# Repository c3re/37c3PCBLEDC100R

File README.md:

# 37c3PCBLEDC100R
Coaster for your drinks with option for LED and microcontroller upgrade.

## Rev.1
### Electrical connections
Important: Do not power the board by USB and an external power supply at the same time!
The Din pin of the first LED is connected to pin D4 (GPIO2) of the Wemos D1 mini. Two of the mounting holes are connected to GND, two of the holes are connected to 5V. You can use this feature to stack multiple 37c3PCBLEDc100R Boards with brass spacers.
### Bug
The revision 1 contains an error in the PCB-Layout! The error affects all LED footprints, the LED pins 1 & 2 are swapped. To fix the Bug, we recommend to bend pin 2 around the PCB edge and solder it on the bottom to the squared pad.

## Rev.2
Bugfixed 
## License
The 37c3 Logo and the dithered image of the bolt cutter were created by Robokid // Luis F. Masallera and Euler Void \
37c3PCBLEDC100R © 2023 by c3RE is licensed under CC BY 4.0. To view a copy of this license, \
visit http://creativecommons.org/licenses/by/4.0/

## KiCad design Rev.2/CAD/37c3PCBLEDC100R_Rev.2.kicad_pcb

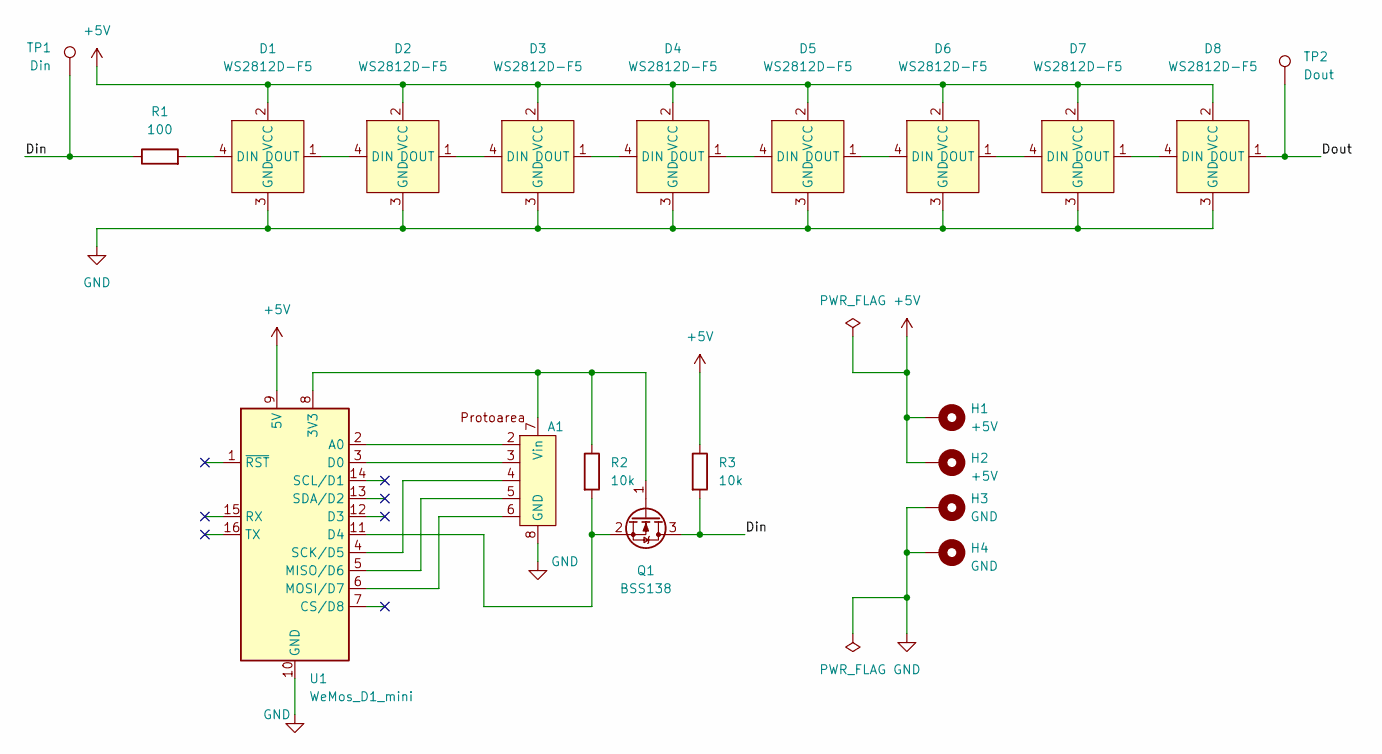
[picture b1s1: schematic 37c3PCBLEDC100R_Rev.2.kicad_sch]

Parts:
A1: Protoarea
D1, D2, D3, D4, D5, D6, D7, D8: WS2812D-F5; WS2812_THT; LCSC Part # C190565
H1, H2: +5V; MountingHole_3.2mm_M3_DIN965_Pad
H3, H4: GND; MountingHole_3.2mm_M3_DIN965_Pad
Q1: BSS138; SOT-23
R1: 100; 1206_combi_handsolder
R2, R3: 10k; 1206_combi_handsolder
TP1: Din; TestPoint_THTPad_D2.5mm_Drill1.2mm
TP2: Dout; TestPoint_THTPad_D2.5mm_Drill1.2mm
U1: WeMos_D1_mini; WEMOS_D1_mini_light

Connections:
+5V: D1.2 (VCC), D2.2 (VCC), D3.2 (VCC), D4.2 (VCC), D5.2 (VCC), D6.2 (VCC), D7.2 (VCC), D8.2 (VCC), H1.1, H2.1, R3.1, U1.9 (5V)
/Din: Q1.3 (D), R1.1, R3.2, TP1.1; also elsewhere on the board
/Dout: D8.1 (DOUT), TP2.1; also elsewhere on the board
GND: A1.8 (GND), D1.3 (GND), D2.3 (GND), D3.3 (GND), D4.3 (GND), D5.3 (GND), D6.3 (GND), D7.3 (GND), D8.3 (GND), H3.1, H4.1, U1.10 (GND)
unnamed: A1.7 (Vin), Q1.1 (G), R2.1, U1.8 (3V3)
unnamed: D1.4 (DIN), R1.2
unnamed: D1.1 (DOUT), D2.4 (DIN)
unnamed: D2.1 (DOUT), D3.4 (DIN)
unnamed: D3.1 (DOUT), D4.4 (DIN)
unnamed: D4.1 (DOUT), D5.4 (DIN)
unnamed: D5.1 (DOUT), D6.4 (DIN)
unnamed: D6.1 (DOUT), D7.4 (DIN)
unnamed: D7.1 (DOUT), D8.4 (DIN)
unnamed: Q1.2 (S), R2.2, U1.11 (D4)
unnamed: A1.2, U1.2 (A0)
unnamed: A1.3, U1.3 (D0)
unnamed: A1.5, U1.5 (MISO/D6)
unnamed: A1.6, U1.6 (MOSI/D7)
unnamed: A1.4, U1.4 (SCK/D5)

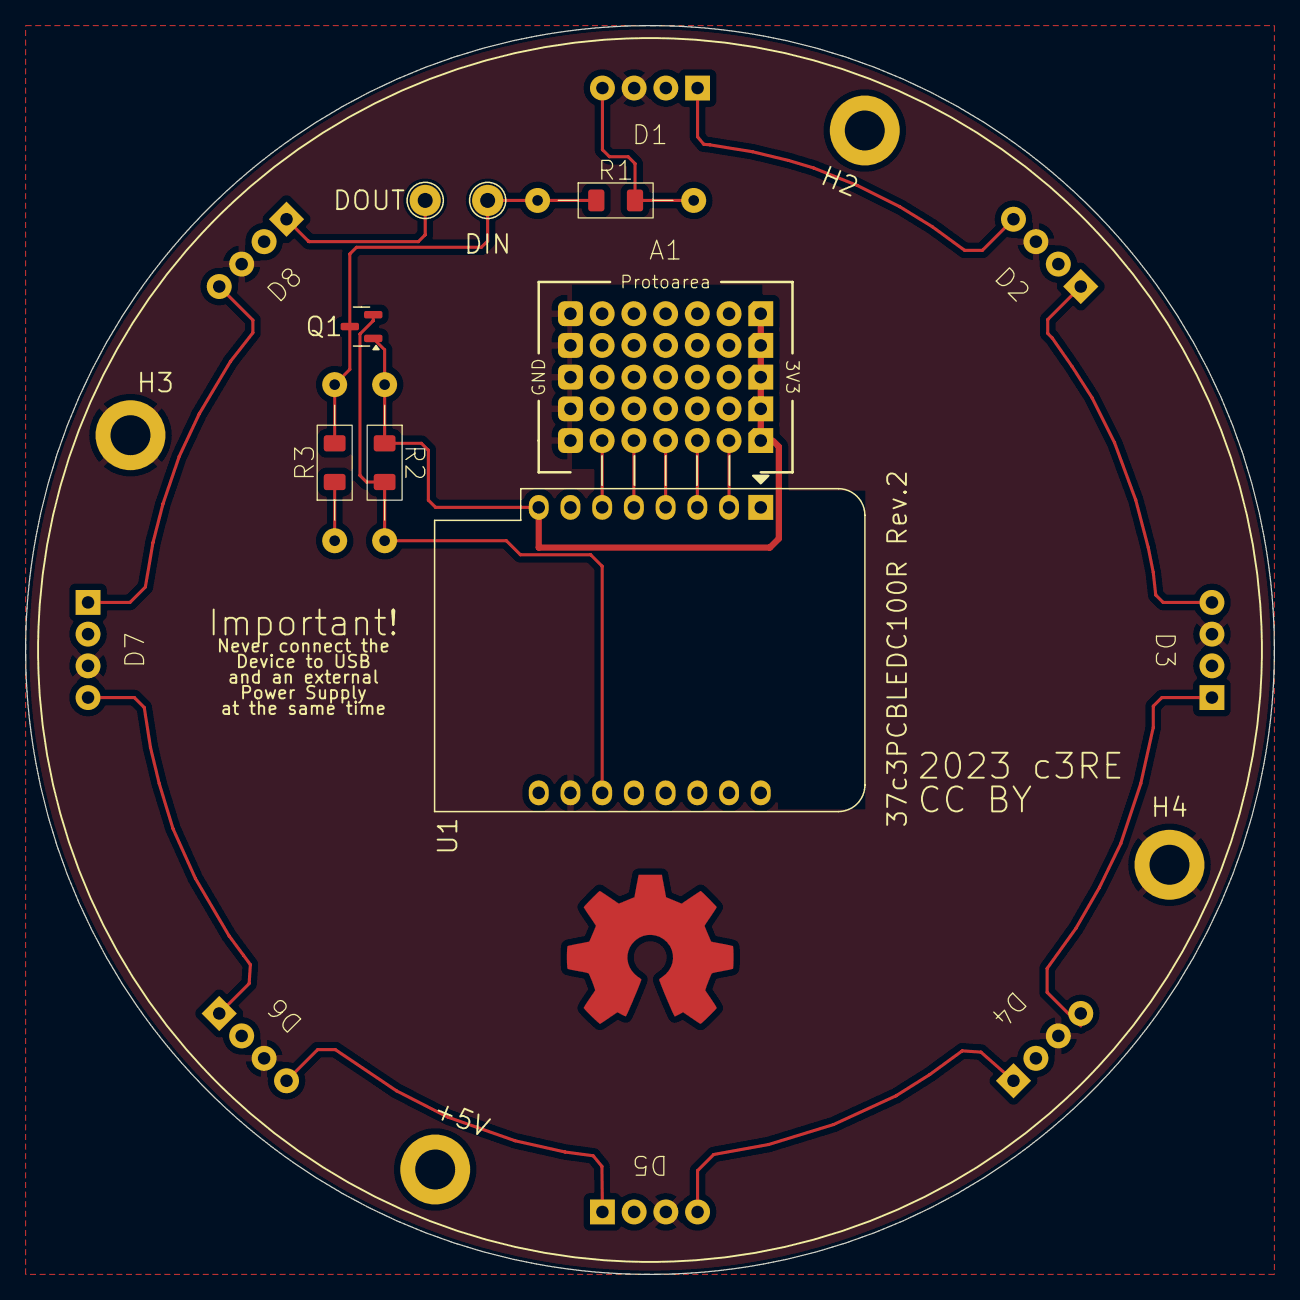
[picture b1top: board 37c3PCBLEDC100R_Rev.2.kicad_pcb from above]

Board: 2 copper layers, 100.0 x 100.0 mm, 20 parts (0 on the bottom side), 19 nets.

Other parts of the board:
DIN: Din; TestPoint_THTPad_D2.5mm_Drill1.2mm
DOUT: Dout; TestPoint_THTPad_D2.5mm_Drill1.2mm

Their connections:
/Din: DIN.1; also elsewhere on the board
/Dout: DOUT.1; also elsewhere on the board

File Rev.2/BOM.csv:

Pos.,Qty.,Designator,Description,Manufacturer,Part-No. (Manufacturer),Vendor,Part-No. (Vendor)
1,1,R1,Metal Film Resistor 100Ohm 250mW,VICO,MF1/4W-100Ω±1%-OT52,LCSC,C2903231
2,2,R2-R3,Metal Film Resistors 10kΩ 250mW,YAGEO,MFR-25FTE52-10K,LCSC,C172967
3,1,Q1,MOSFET N-CH 50V 220mA SOT-23,KUU,BSS138,LCSC,C3015220
4,8,D1-D8,D=5mm RGB LED(Built-in IC),Worldsemi,WS2812D-F5,LCSC,C190565
5,4,na,Spacer,Shuntian,M3X25+6,LCSC,C775782

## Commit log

2023-12-20 Added License text
2023-12-20 Image added
2023-12-20 Imagesize reduced
2023-12-23 Added assembly instructions
2023-12-25 Added some descriptions
2024-01-07 Bugfixed Rev.2 added
2024-10-06 Updated Libs & changes on Top Silkscreen
2024-10-06 Generated new Gerber-Files
2024-10-30 Create PARTS with components to buy and solder
2024-11-24 Some minor fixes
2024-11-24 BOM revised
2024-12-29 add construction inlay
